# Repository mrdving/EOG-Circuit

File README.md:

# EOG-Circuit
An EOG circuit that gets the signal from the eye movement, and uses the output to control a game

EOG-TestDrive is the Unity Game. Created with Unity Engine version 2019.4.17f1
In the game, run Game scene and press space bar to begin, 'a' to move left, 'd' to move right

Keyboard_test.ino is the Script that runs in Arduino. Beware that only certain modules support the <Keyboard> package, such as Leonardo, but not Uno

CircuitDiagram Provides information on the components and connections

PCB contains KiCad file open with KiCad

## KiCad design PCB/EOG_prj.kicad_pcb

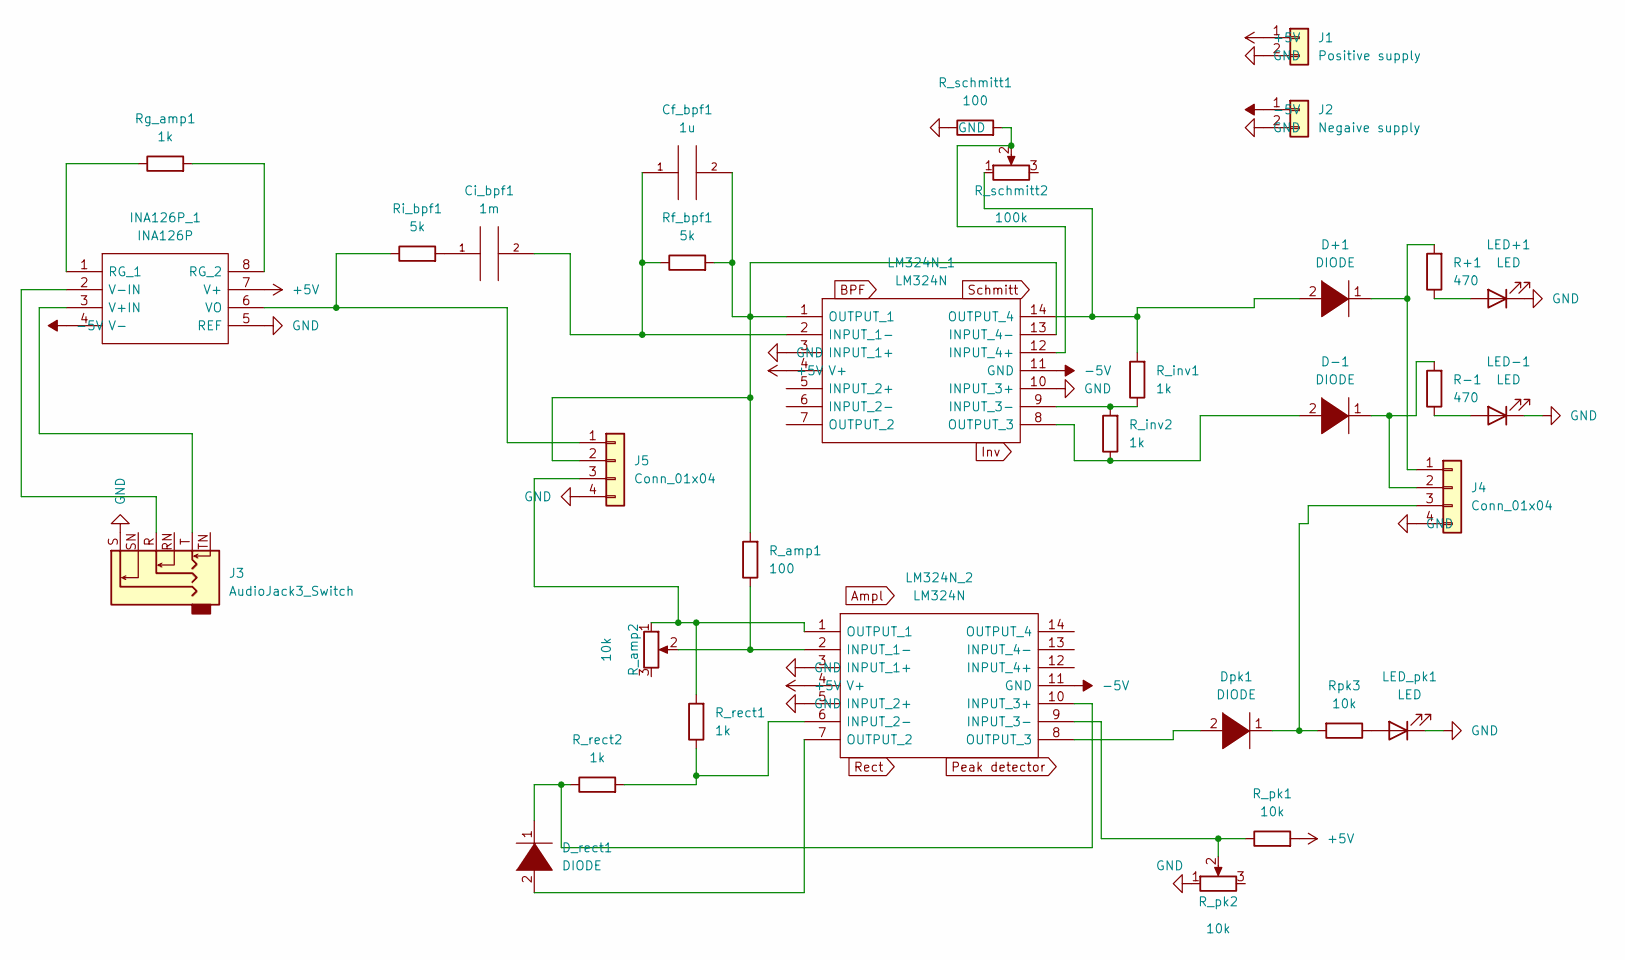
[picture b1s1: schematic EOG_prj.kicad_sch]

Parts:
Cf_bpf1: 1u; C_Radial_D5.0mm_H5.0mm_P2.00mm
Ci_bpf1: 1m; C_Radial_D12.5mm_H20.0mm_P5.00mm
D+1: DIODE; D_A-405_P10.16mm_Horizontal
D-1: DIODE; D_A-405_P10.16mm_Horizontal
D_rect1: DIODE; D_A-405_P10.16mm_Horizontal
Dpk1: DIODE; D_A-405_P10.16mm_Horizontal
INA126P_1: INA126P; DIP794W53P254L959H508Q8N; Manufacturer_Part_Number INA126P; Mouser Part Number 595-INA126P
J1: Positive supply; SolderWire-0.1sqmm_1x02_P3.6mm_D0.4mm_OD1mm
J2: Negaive supply; SolderWire-0.1sqmm_1x02_P3.6mm_D0.4mm_OD1mm
J3: AudioJack3_Switch; Jack_3.5mm_CUI_SJ1-3525N_Horizontal
J4, J5: Conn_01x04; SolderWire-0.1sqmm_1x04_P3.6mm_D0.4mm_OD1mm
LED+1: LED; LED_D3.0mm_Horizontal_O3.81mm_Z6.0mm
LED-1: LED; LED_D3.0mm_Horizontal_O3.81mm_Z6.0mm
LED_pk1: LED; LED_D3.0mm_Horizontal_O3.81mm_Z6.0mm
LM324N_1, LM324N_2: LM324N; DIP794W56P254L1905H533Q14N; Manufacturer_Part_Number LM324N; Mouser Part Number 595-LM324N
R+1: 470; R_Axial_DIN0207_L6.3mm_D2.5mm_P10.16mm_Horizontal
R-1: 470; R_Axial_DIN0207_L6.3mm_D2.5mm_P10.16mm_Horizontal
R_amp1: 100; R_Axial_DIN0207_L6.3mm_D2.5mm_P10.16mm_Horizontal
R_amp2: 10k; Potentiometer_Bourns_3339W_Horizontal
R_inv1, R_inv2: 1k; R_Axial_DIN0207_L6.3mm_D2.5mm_P10.16mm_Horizontal
R_pk1: 10k; R_Axial_DIN0207_L6.3mm_D2.5mm_P10.16mm_Horizontal
R_pk2: 10k; Potentiometer_Bourns_3339W_Horizontal
R_rect1, R_rect2: 1k; R_Axial_DIN0207_L6.3mm_D2.5mm_P10.16mm_Horizontal
R_schmitt1: 100; R_Axial_DIN0207_L6.3mm_D2.5mm_P10.16mm_Horizontal
R_schmitt2: 100k; Potentiometer_Bourns_3339W_Horizontal
Rf_bpf1: 5k; R_Axial_DIN0207_L6.3mm_D2.5mm_P10.16mm_Horizontal
Rg_amp1: 1k; R_Axial_DIN0207_L6.3mm_D2.5mm_P10.16mm_Horizontal
Ri_bpf1: 5k; R_Axial_DIN0207_L6.3mm_D2.5mm_P10.16mm_Horizontal
Rpk3: 10k; R_Axial_DIN0207_L6.3mm_D2.5mm_P10.16mm_Horizontal

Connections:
+5V: INA126P_1.7 (V+), J1.1, LM324N_1.4 (V+), LM324N_2.4 (V+), R_pk1.2
-5V: INA126P_1.4 (V-), J2.1, LM324N_1.11 (GND), LM324N_2.11 (GND)
GND: INA126P_1.5 (REF), J1.2, J2.2, J3.S, J4.4, J5.4, LED+1.1 (K), LED-1.1 (K), LED_pk1.1 (K), LM324N_1.3 (INPUT_1+), LM324N_1.10 (INPUT_3+), LM324N_2.3 (INPUT_1+), LM324N_2.5 (INPUT_2+), R_pk2.1, R_schmitt1.1
unnamed: Cf_bpf1.1, Ci_bpf1.2, LM324N_1.2 (INPUT_1-), Rf_bpf1.1
unnamed: Cf_bpf1.2, J5.2, LM324N_1.1 (OUTPUT_1), LM324N_1.13 (INPUT_4-), R_amp1.2, Rf_bpf1.2
unnamed: Ci_bpf1.1, Ri_bpf1.2
unnamed: INA126P_1.1 (RG_1), Rg_amp1.1
unnamed: INA126P_1.2 (V-IN), J3.R
unnamed: INA126P_1.3 (V+IN), J3.T
unnamed: INA126P_1.6 (VO), J5.1, Ri_bpf1.1
unnamed: INA126P_1.8 (RG_2), Rg_amp1.2
unnamed: D+1.1 (A), J4.1, R+1.2
unnamed: D-1.1 (A), J4.2, R-1.2
unnamed: Dpk1.1 (A), J4.3, Rpk3.2
unnamed: LED+1.2 (A), R+1.1
unnamed: LED-1.2 (A), R-1.1
unnamed: LED_pk1.2 (A), Rpk3.1
unnamed: D-1.2 (K), LM324N_1.8 (OUTPUT_3), R_inv2.1
unnamed: LM324N_1.9 (INPUT_3-), R_inv1.1, R_inv2.2
unnamed: LM324N_1.12 (INPUT_4+), R_schmitt1.2, R_schmitt2.2
unnamed: D+1.2 (K), LM324N_1.14 (OUTPUT_4), R_inv1.2, R_schmitt2.1
unnamed: J5.3, LM324N_2.1 (OUTPUT_1), R_amp2.1, R_rect1.2
unnamed: LM324N_2.2 (INPUT_1-), R_amp1.1, R_amp2.2
unnamed: LM324N_2.6 (INPUT_2-), R_rect1.1, R_rect2.2
unnamed: D_rect1.2 (K), LM324N_2.7 (OUTPUT_2)
unnamed: Dpk1.2 (K), LM324N_2.8 (OUTPUT_3)
unnamed: LM324N_2.9 (INPUT_3-), R_pk1.1, R_pk2.2
unnamed: D_rect1.1 (A), LM324N_2.10 (INPUT_3+), R_rect2.1

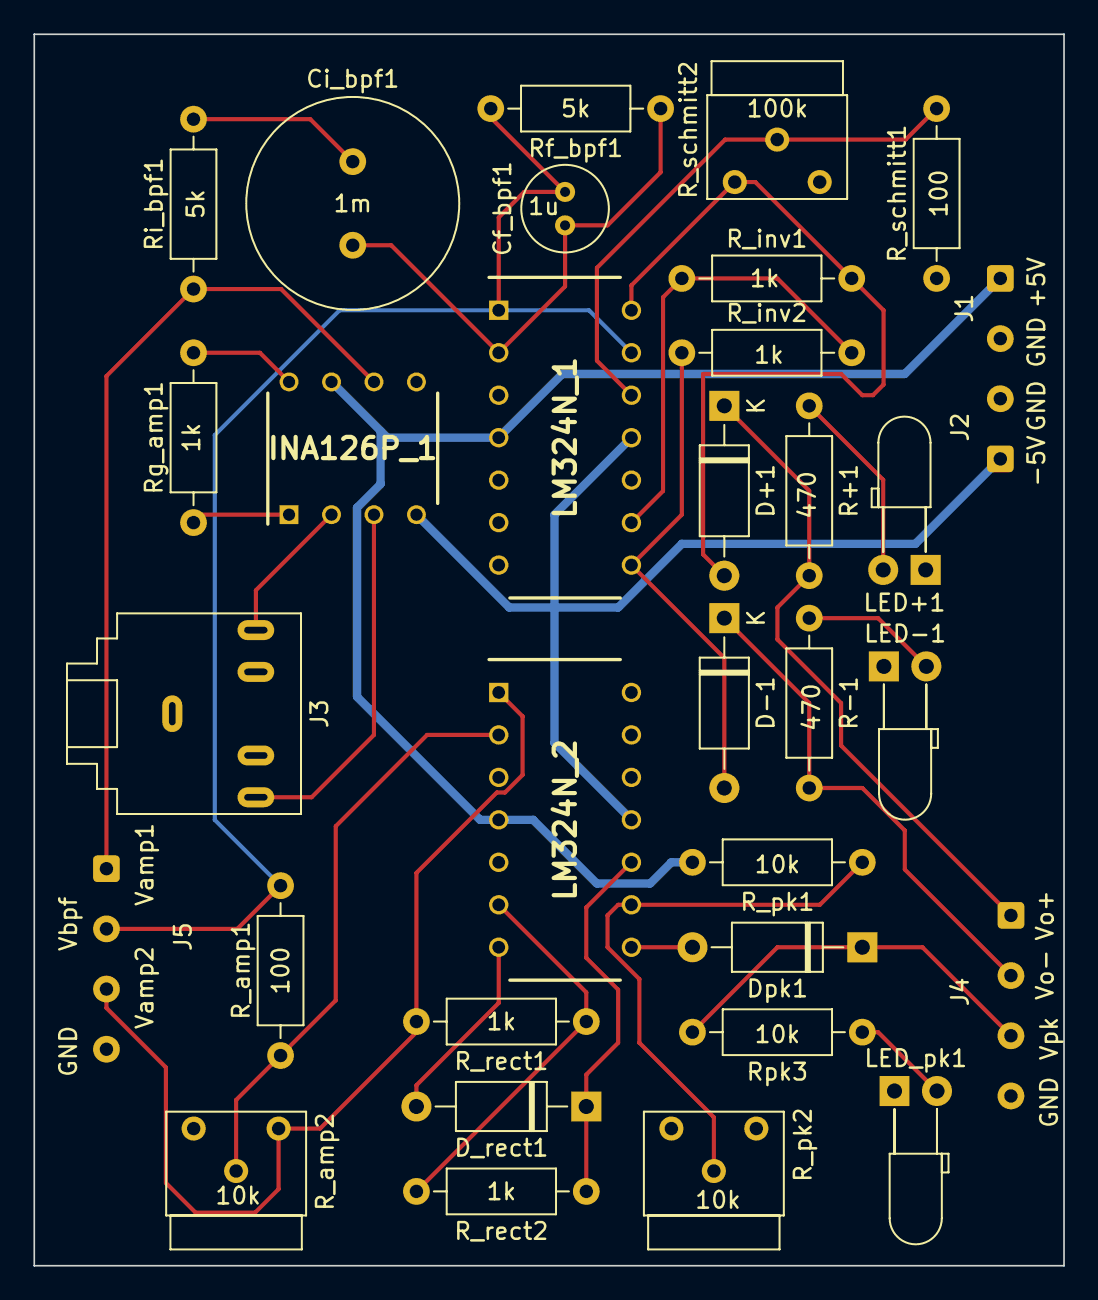
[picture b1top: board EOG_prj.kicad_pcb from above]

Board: 2 copper layers, 61.6 x 73.7 mm, 33 parts (0 on the bottom side), 28 nets.

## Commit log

2022-09-07 PCB
    PCB and schematics
2022-09-07 Circuit Diagram
2022-09-07 CircuitDiagram : Rename
2022-09-07 CircuitDiagram
2022-09-07 Game : Create Folder
2022-09-07 Game : Upload 1
    Project Settings, Packages, obj, Logs, .csproj and .sln files
2022-09-07 ArduinoControl upload
2022-09-07 Game : Upload
